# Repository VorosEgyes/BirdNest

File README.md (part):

# BirdNest ESP32-CAM Project

BirdNest is a battery-aware ESP32-CAM wildlife and bird nest monitoring project built with PlatformIO and Arduino. It captures photos on schedule or command, sends images and status updates to Telegram, and supports MQTT telemetry for smart home and IoT integrations. The firmware includes deep sleep power saving, OTA remote updates, WiFi recovery logic, DS18B20 temperature monitoring, and calibrated battery voltage reporting for reliable long-term outdoor operation.

**Single firmware binary model.** All cameras share one firmware build. Device-specific identity (label, OTA hostname, AP name) is stored in NVS at runtime, with a MAC-address-based fallback for first boot. Identity can be changed remotely via Telegram commands without reflashing.

**GitHub OTA.** Starting from v0.1.0, firmware releases are published to GitHub automatically via CI. Each device can check for and install updates over HTTPS, with SHA-256 verification and rollback support. Updates are controlled via Telegram commands at runtime. In the current firmware, the OTA install path is gated by network health and battery checks; weak RSSI alone no longer blocks installation, but the device still requires a live Wi-Fi connection and a valid OTA partition layout.

## Hardware Design Files (KiCad)

The hardware design assets are stored in `hardware/BirdNest_pcb/`.

- Schematic: `hardware/BirdNest_pcb/BirdNest_pcb.kicad_sch`
- PCB layout: `hardware/BirdNest_pcb/BirdNest_pcb.kicad_pcb`
- KiCad project: `hardware/BirdNest_pcb/BirdNest_pcb.kicad_pro`
- KiCad project local settings: `hardware/BirdNest_pcb/BirdNest_pcb.kicad_prl`
- Backup folder: `hardware/BirdNest_pcb/BirdNest_pcb-backups/`

### 3D PCB View

---

## Complete Hardware Pin Mapping (AI-Thinker ESP32-CAM)

| Function | Pin | Notes |
|---|---|---|
| XCLK | GPIO0 | 20 MHz camera clock |
| Camera D0 (Y2) | GPIO5 | Data pin |
| Camera D1 (Y3) | GPIO18 | Data pin |
| Camera D2 (Y4) | GPIO19 | Data pin |
| Camera D3 (Y5) | GPIO21 | Data pin |
| Camera D4 (Y6) | GPIO36 | Data pin |
| Camera D5 (Y7) | GPIO39 | Data pin |
| Camera D6 (Y8) | GPIO34 | Data pin |
| Camera D7 (Y9) | GPIO35 | Data pin |
| HREF | GPIO23 | Control line |
| VSYNC | GPIO25 | Control line |
| PCLK | GPIO22 | Control line |
| SDA (I2C) | GPIO26 | Camera I2C data |
| SCL (I2C) | GPIO27 | Camera I2C clock |
| OneWire (DS18B20) | GPIO13 | OneWire bus |
| ADC (Battery) | GPIO12 | Battery voltage measurement |
| Flash LED | GPIO4 | PWM control |

## Hardware modification

The current board revision uses a more elaborate power-management section around the ESP32-CAM module than the original single-regulator layout. In the current KiCad schematic, the power path is implemented with a ME2188-based regulator stage together with battery switching, UVLO sensing, and a 2.5 V reference network for battery monitoring.

Current hardware notes from the schematic:
- The firmware still targets the standard AI-Thinker ESP32-CAM pinout described above.
- The board includes battery-related nets such as BAT_RAW and BAT_MON, plus UVLO control/sense circuitry for low-voltage protection.
- The schematic also routes the DS18B20 one-wire sensor and a PIR signal net in addition to the camera and power rails.

---

## Complete Boot Sequence (PHASE 1 in setup())

1. **Serial init** — initialize UART at 115200 baud for debug output
2. **tempInit()** — DS18B20 on GPIO13 OneWire bus with internal pull-up
3. **batteryInit()** — GPIO12 ADC setup for battery voltage reading
4. **WiFi connect phase** — STA connect with boot retries; rescue captive portal on repeated failures; deep-sleep fallback when boot connectivity cannot be recovered
5. **otaInit()** and startup OTA window — check for ArduinoOTA updates (`OTA_STARTUP_WINDOW_SEC`, or `OTA_RECOVERY_WINDOW_SEC` when recovery is armed)
5b. **ghOtaInit()** — initialize GitHub OTA module after the ArduinoOTA window settles; confirm post-install rollback health if `ESP_OTA_IMG_PENDING_VERIFY`; run auto-check and install if `otaAuto=true`
6. **syncTimeIfNeeded()** — NTP sync with up to 30 retries, 200ms between each
7. **telegramInit()** and startup message processing — initialize Telegram bot and handle first message
8. **nightSleepIfNeeded()** — if after sunset, sleep until sunrise using week-number lookup table
9. **Welcome / startup photo decision** — send welcome message only on normal boot; on timer wake, capture+send photo if maintenance mode is off
10. **Final deep sleep decision** — call `esp_deep_sleep_start()` when sleep interval is enabled and OTA is not active

---

## Photo Capture Sequence (PHASE 2)

1. **cameraInit()** — configure AI-Thinker pins (D0-D7, HREF, VSYNC, PCLK, XCLK, SCCB), JPEG mode, and grab mode
2. **PSRAM profile select** — if PSRAM is present use PSRAM frame/quality flags and `fb_count=2`, otherwise fallback profile with `fb_count=1`
3. **Init resilience** — handle `ESP_ERR_INVALID_STATE` with deinit+retry, plus second init retry after 500 ms
4. **Sensor tuning** — apply white balance, AGC/AEC settings, orientation (`/mirror` and `/flip`), and light-based OV2640 register ladder
5. **Warm-up capture phase** — capture `CAMERA_WARMUP_FRAMES` frames (current active profile: 4), with frame-grab retries (`CAMERA_FB_GET_RETRIES`)
6. **Final fallback capture** — if all warm-up grabs fail, run one final retried frame-grab attempt
7. **HTTPS multipart upload** — send Telegram `sendPhoto` request with chunked JPEG write (`8 KB` chunks) over `WiFiClientSecure`
8. **Response validation** — parse response body and treat only `"ok":true` as success; store detailed failure reason otherwise
9. **Upload retry loop** — outer retry in `captureAndSendPhoto()` with WiFi reconnect and progressive backoff (`PHOTO_SEND_RETRY_BACKOFF_MS * attempt`)
10. **cameraDeinit()** — deinitialize camera and wait 100 ms before any next init

---

## Telegram Command Processing (PHASE 3 in loop())

- 5-second polling interval
- Update ID persistence every 30 seconds
- Command table: `/status`, `/help`, `/photo`, `/sleepXX`, `/maint_on`, `/maint_off`, `/netdiag`, `/reboot`, `/reboot_ota`, `/setlabel`, `/sethostname`, `/bootstrap_prepare`, `/reset_config`, `/debug0|1|2`, `/mirror0|1`, `/flip0|1`, `/battcal`, `/battcalset`, `/battcalclear`, `/mqtt`, `/mqttset`, `/mqtttopic`, `/mqtttopic_reset`, `/mqttoff`, `/otastatus`, `/otaupdate_check`, `/otaupdate_now`, `/otaupdate_auto_on`, `/otaupdate_auto_off`, `/otachannel`, `/otatoken_set`, `/otatoken_clear`
- `/status` returns status only; full command listing is in `/help`
- Callback execution for each command

---

## Deep Sleep & Wakeup (PHASE 4)

- ESP32 hibernates: CPU off, RTC timer running
- Current draw: 100–500 µA during deep sleep
- Wakeup detection via `esp_sleep_get_wakeup_cause()`
- `fromSleep` flag behavior: sets `fromSleep` to true on wake, false on normal boot

---

## Detailed Module Descriptions

### WiFi Manager
- Telegram credential check from NVS (`botToken`, `chatId`, `debugChatId`) before connect flow
- Fail-fast STA reconnect path (`WIFI_FAIL_FAST_SEC`) when captive portal is disabled
- Rescue captive portal opens on missing Telegram fields or repeated boot failures
- Persistent WiFi failure counter (`wifiFail`) in NVS; reset to 0 on successful connect

## WiFi Connection Lifecycle (full program behavior)

### 1) Boot-time connection strategy

- The device first loads Telegram credentials and WiFi failure counter from NVS.
- If captive portal is disabled and Telegram fields are present, it tries normal STA reconnect first (`wifiInit()`).
- Boot retries are applied by the main program:
	- `WIFI_BOOT_CONNECT_RETRIES`
	- `WIFI_BOOT_RETRY_BACKOFF_SEC`
- In fail-fast mode, each WiFi attempt uses `WIFI_FAIL_FAST_SEC` timeout.

### 2) Rescue captive portal fallback

- If Telegram credentials are missing, captive portal is opened immediately.
- If `WIFI_ENABLE_CAPTIVE_PORTAL != 0`, portal path is always allowed.
- With repeated STA failures, rescue portal opens after `WIFI_RESCUE_FAIL_COUNT` failures.
- Optional periodic rescue windows use `WIFI_RESCUE_PORTAL_INTERVAL_FAILS`.
- Portal timeout uses `WIFI_RESCUE_PORTAL_TIMEOUT` (rescue) or `CONFIG_PORTAL_TIMEOUT` (normal).
- Captive portal includes custom fields for Telegram token, main chat ID, and debug chat ID.

### 3) Boot failure fallback (failsafe deep sleep)

- If WiFi cannot be established after boot retries, device enters deep sleep backoff.
- Default backoff path uses `WIFI_RETRY_BACKOFF_SEC`.
- If OTA recovery is armed, recovery sleep timing is used instead (`otaGetRecoverySleepSeconds`), including low-battery protection.

### 4) Runtime link-loss handling (while running)

- The loop continuously checks WiFi state before network-heavy tasks.
- On disconnect:
	- reconnect attempts are triggered every `WIFI_RUNTIME_RECONNECT_INTERVAL_SEC`
	- diagnostics counters are updated (`/netdiag`)
- If disconnected too long, failsafe reboot is triggered after `WIFI_RUNTIME_REBOOT_AFTER_SEC`.

### 5) OTA interaction

- OTA processing runs first in loop (`otaLoop()`).
- While OTA is active, other network work is deferred.
- Deep sleep is suppressed during active OTA transfer.
- Startup OTA polling window is dynamic: normal `OTA_STARTUP_WINDOW_SEC`, or extended `OTA_RECOVERY_WINDOW_SEC` when recovery mode is armed.
- OTA transfer watchdog restarts the device if no OTA events arrive for `OTA_STALL_TIMEOUT_SEC`.

### 6) Maintenance mode behavior

- Maintenance mode suppresses automatic sleep/photo cycle decisions, but does not bypass WiFi requirements.
- If network quality is poor, runtime reconnect/failsafe logic still applies.
- Manual diagnostics command: `/netdiag`.

### Telegram
- Bot token stored in NVS
- Poll loop every 5 seconds
- NVS persistence of sleep/maintenance settings
- `lastMsgId` tracking for message updates
- `/help` provides the full command list, while `/status` stays focused on runtime state

### Camera
- AI-Thinker pin mapping: D0–D7 data, HREF/VSYNC/PCLK control, XCLK 20 MHz
- PSRAM-aware frame profile (`CAMERA_FRAMESIZE_*`, `CAMERA_JPEG_QUALITY_*`, `fb_count`)
- Warm-up frames from build flag (`CAMERA_WARMUP_FRAMES`, active profile uses 4)
- JPEG capture and frame buffer
- Upload via HTTPS multipart POST using `WiFiClientSecure` and `writeAll()` helper
- Manual lowlight/day exposure register ladder based on ambient light register (`0x2f`)
- Multi-attempt Telegram photo upload with reconnect/backoff on failure
- Remote error diagnostics via Telegram debug messages (serial not required)

### Camera Exposure / Lowlight Logic (actual implementation)
- Ambient light value is read from sensor register `0x2f`
- `CAMERA_DAY_THRESHOLD` separates lowlight and daylight branches
- AGC is disabled (`set_gain_ctrl(0)`), gain is manual (`set_agc_gain(0)`), and exposure is controlled by register ladder writes
- A post-frame fine-tuning pass adjusts `0x47`, `0x2a`, and `0x2b` for very low to medium light
- Current implementation does not use `CAMERA_DYNAMIC_EXPOSURE_PROFILE`, `CAMERA_DAY_*`, or `CAMERA_LOWLIGHT_*` flag families

### Photo Upload Reliability and Remote Diagnostics
- Upload attempts are retried with progressive backoff and WiFi reconnect between tries.
- Retry behavior is configurable with:
	- `PHOTO_SEND_MAX_RETRIES`
	- `PHOTO_SEND_RETRY_BACKOFF_MS`
	- `CAMERA_FB_GET_RETRIES`
	- `CAMERA_FB_GET_RETRY_DELAY_MS`
- On each failed attempt, the device sends detailed failure reason to Telegram debug chat.
- Final failure message includes the last known upload error cause.

Common remote error reasons (`cameraGetLastError`):

- `empty_chat_id` - no chat ID was provided
- `missing_bot_token` - Telegram bot token is missing/empty
- `wifi_not_connected_before_upload` - WiFi dropped before upload start
- `telegram_tls_connect_failed` - TLS connection to `api.telegram.org:443` failed
- `camera_fb_get_failed_final` - frame grab failed after warm-up and final fallback attempt
- `upload_failed_headers_or_prefix` - multipart request header/prefix write failed
- `upload_chunk_write_failed_offset_N` - JPEG data upload interrupted at byte offset
- `upload_multipart_tail_failed` - multipart tail write failed
- `telegram_response_not_ok_empty_body` - Telegram returned non-OK with empty body
- `telegram_response_not_ok_...` - Telegram API responded with `ok:false` and body snippet

### Temperature
- DS18B20 on GPIO13 OneWire protocol with internal pull-up
- One blocking conversion is performed on cache miss; the result is reused for up to 60 seconds across status, MQTT, and photo-caption reads.
- If no sensor is detected during initialization, reads return `-127.0` without polling the OneWire bus.

### Battery
- ADC on GPIO12 with resistor divider formula
- Two-point calibration math using `bCalA`/`bCalB`
- GPIO12 is ADC2 on ESP32. While WiFi is connected, ADC2 sampling is not reliable/available, so the firmware returns the last cached valid value.
- A fresh battery sample is taken during boot before WiFi connect (`batteryRefresh()` in setup), then reused during active WiFi on ADC2 hardware.
- `/status` reports that cached value on ADC2+WiFi. This is typically the most recent wake-time sample.
- If `/status` is sent while the device is in deep sleep, it is processed after wake, so battery data in the reply reflects the new measurement from that wake cycle.

### Runtime Device Identity

All cameras run the same firmware binary. Each device's identity is stored in NVS and loaded at every boot.

| NVS key | Default | Description |
|---|---|---|
| `devLabel` | `BirdNest-XXXXXXXX` (MAC) | Human-readable device name |
| `otaHost` | `birdnest-xxxxxxxx` (MAC) | ArduinoOTA mDNS hostname |
| AP name | derived from `devLabel` + `-cfg` | Captive portal AP name (not stored separately) |

On first boot the label and hostname are generated from the lower 32 bits of the chip MAC address, so multiple devices with the same factory firmware never collide on the same LAN.

Telegram commands:
- `/setlabel <name>` — change device label (persisted in NVS, affects MQTT topics and photo captions)
- `/sethostname <name>` — change ArduinoOTA hostname (reboot required to apply mDNS)
- `/status` and welcome message show current label and OTA hostname

---

### ArduinoOTA (local network upload)
- Startup OTA window: `OTA_STARTUP_WINDOW_SEC` (default 8 s)
- Extended recovery window: `OTA_RECOVERY_WINDOW_SEC` (default 120 s) when recovery latch is armed
- OTA stall watchdog: restart if transfer is idle for `OTA_STALL_TIMEOUT_SEC`
- Recovery sleep policy: `OTA_RECOVERY_SLEEP_SEC`, with low-battery fallback `OTA_RECOVERY_LOW_BATTERY_SLEEP_SEC` below `OTA_RECOVERY_MIN_BATTERY_V`
- Recovery state is persisted in NVS via `otaArmed` and `otaCycles`
- `/reboot_ota` arms recovery and reboots — opens an extended OTA window for PlatformIO upload

---

### GitHub OTA (automatic over-the-internet updates)

Starting from v0.1.0, every `v*` git tag triggers a CI build that publishes a single firmware binary and `ota-manifest.json` to GitHub Releases. Devices can check and install these releases over HTTPS without physical access.

#### How it works

1. **Check**: device queries `api.github.com/repos/VorosEgyes/BirdNest/releases`, finds the best candidate by SemVer and channel (stable/beta), downloads `ota-manifest.json`.
2. **Install gate**: battery ≥ max(3.60 V, `manifest.min_battery_v`), WiFi stable.
3. **Install**: streams the `.bin` via HTTPS, verifies SHA-256 incrementally, writes to the inactive OTA partition, reboots.
4. **Health confirm**: on first boot after install, pings `api.github.com/rate_limit` up to 3 times; if any succeed, marks the image valid and cancels rollback.

#### Partition table requirement

GitHub OTA install requires an A/B OTA partition layout (`partitions_ota_4m.csv`). Devices previously flashed with `min_spiffs.csv` (single app partition) will run all GitHub OTA code normally but **install will be blocked** with reason `no_update_partition` until the device receives a full flash. This is why the first installation should be done over USB/serial for a new or previously single-partition device.

| Scenario | ArduinoOTA upload | GitHub OTA install |
|---|---|---|
| Device with `partitions_ota_4m.csv` | ✅ | ✅ |
| Device with `min_spiffs.csv` (old layout) | ✅ | ❌ blocked |

#### First-install / partition migration guide

To migrate an existing camera from `min_spiffs` to OTA partitions:

1. Connect via USB.
2. Run a full flash (includes partition table + bootloader + firmware):
   ```bash
   pio run -e cam1 -t upload --upload-port /dev/cu.usbserial-XXXX
   # or cam2, cam3, cam4 — all envs produce the same binary
   ```
3. After this one-time flash, all future updates can be done via GitHub OTA with no physical access.

For cameras only reachable via ArduinoOTA, use `/bootstrap_prepare` before the USB flash session to ensure maintenance mode is on and sleep is off.

#### Bootstrap preflight command

`/bootstrap_prepare` — run this before any first-install or partition migration session:
- Sets maintenance mode ON (suppresses deep sleep)
- Sets sleep interval to 0
- Disables WiFi modem sleep
- Arms ArduinoOTA recovery
- Runs and reports a preflight check:
  - Battery ≥ `BOOTSTRAP_MIN_BATTERY_V` (default 3.80 V)
  - WiFi connected and RSSI ≥ `BOOTSTRAP_MIN_RSSI_DBM` (default −82 dBm)
  - Telegram credentials present
  - OTA update partition reachable

Reports `READY` or `NOT READY` with per-check detail.

#### GitHub OTA Telegram commands

| Command | Description |
|---|---|
| `/otastatus` | JSON status: current version, channel, auto mode, pending target, last reason |
| `/otaupdate_check` | Query GitHub releases; report available version or no-update |
| `/otaupdate_now` | Check and immediately install if update found |
| `/otaupdate_auto_on` | Enable automatic check+install on every boot |
| `/otaupdate_auto_off` | Disable automatic updates (manual only) |
| `/otachannel stable\|beta` | Switch release channel |
| `/otatoken_set <token>` | Set GitHub API token (private repos; message auto-deleted) |
| `/otatoken_clear` | Clear token; drops pending private target |

#### Versioning and CI release workflow

- `FW_VERSION` is injected at build time from the nearest git tag via `scripts/fw_version_from_git.py`.
- Local/untagged builds use `0.0.0-dev` as fallback.
- The shared PlatformIO environment pins `espressif32@7.0.1` (Arduino ESP32
  2.x); upgrading to Arduino ESP32 3.x requires camera and OTA API migration.
- CI (`release-ota.yml`) triggers on any `v*` tag push:
  - Builds `[env:release]` (same binary as camX envs)
  - Calculates SHA-256
  - Uploads `birdnest-esp32cam-vX.Y.Z.bin` and `ota-manifest.json` to GitHub Releases
- Devices on stable channel only see non-prerelease tags; beta channel sees prerelease tags too.

#### Check/backoff policy

- Auto-check runs at most once per day (`GH_OTA_DAILY_CHECK_SEC`).
- WiFi instability increments a fail streak with exponential backoff: 6 h → 12 h → 24 h → 48 h max.
- Backoff is reset after 2 consecutive stable WiFi cycles.
- Manual `/otaupdate_check` and `/otaupdate_now` bypass daily interval and backoff.
- The Telegram TLS connection is closed before the automatic GitHub health probe.
  The probe parses only the rate-limit field it needs; failures report HTTP,
  transport, response length and JSON parsing details through Telegram.
  If an automatic check ends in a crash, the next boot disables automatic checks
  and reports the retained OTA stage and minimum free task stack in bytes through
  Telegram. Manual checks remain available; use `/otaupdate_auto_on` to retry.

#### GitHub OTA NVS keys (namespace: `birdnest_gh`)

| Key | Type | Description |
|---|---|---|
| `otaAuto` | bool | Auto-update enabled |
| `otaChannel` | string | `stable` or `beta` |
| `otaToken` | string | GitHub API token (private repos) |
| `otaLastChk` | uint32 | Unix timestamp of last successful check |
| `otaWifiFail` | uint16 | Consecutive WiFi stability failures |
| `otaChkFail` | uint16 | Consecutive check failures |
| `otaWifiOk` | uint8 | Consecutive stable cycles (for backoff reset) |
| `otaBackoff` | uint32 | Backoff-end timestamp (0 = no backoff) |
| `otaTarget` | string | JSON-serialized pending install target |
| `otaLastReason` | string | Last OTA block/fail reason code |
| `otaRebootFlg` | bool | Set before install reboot, cleared on next boot |
| `otaLastTgt` | string | Version string of last attempted install |

### MQTT
- Runtime MQTT client with automatic reconnect
- JSON status publish to a configurable state topic (channel)
- Config stored in NVS and editable from Telegram
- Supports auth and no-auth brokers
- Periodic publish (`MQTT_STATUS_INTERVAL_SEC`) and immediate publish on boot/config change
- LWT availability support (`online` / `offline`, retained)
- Separate state/event/availability topic model
- Payload schema versioning (`schema_version`)
- GitHub OTA events published via `mqttPublishOtaEvent()` to the event topic

---

## MQTT Setup and Usage

### Default Topics

If no custom topic is set, these topics are used:

- State topic: `birdnest/<deviceLabel>/status`
- Event topic: `birdnest/<deviceLabel>/event`
- Availability topic: `birdnest/<deviceLabel>/availability`

Where `<deviceLabel>` is the runtime device identity loaded from NVS (see Runtime Device Identity section). The default is `BirdNest-XXXXXXXX` based on MAC address.

If you set a custom topic with `/mqtttopic`:

- The custom value is used as the state topic.
- If it ends with `/status`, event and availability are derived as sibling topics.
- Otherwise `/event` and `/availability` are appended.

### Telegram Commands for MQTT

- `/mqtt` - show current MQTT config and active channel
- `/mqttset <ip-or-host> <port> <user|-> <pass|->` - set broker and auth in one message
- `/mqtttopic <topic>` - set custom publish channel/topic
- `/mqtttopic_reset` - reset topic to default (`birdnest/CAMERA_LABEL/status`)
- `/mqttoff` - disable MQTT and clear broker credentials

`/mqtt` now reports:

- State topic
- Event topic
- Availability topic
- Schema version

### One-message setup examples

- Auth enabled:
	- `/mqttset 192.168.1.100 1883 mqtt_user mqtt_pass`
- No auth:
	- `/mqttset 192.168.1.100 1883 - -`

### Channel/topic examples

- Set custom channel:
	- `/mqtttopic birdnest/BirdNestCam1/status`
- Reset to default channel:
	- `/mqtttopic_reset`

### Published payloads

State payload (`status`) is JSON and includes:

- `schema_version`
- `device`
- `reason` (`boot`, `periodic`, `manual`, `config_updated`, ...)
- `ip`
- `rssi`
- `uptime_s`
- `temp_c`
- `battery_v`
- `battery_pct`
- `maint`

Event payload (`event`) is JSON and includes:

- `schema_version`
- `device`
- `event`
- `detail`
- `uptime_s`

GitHub OTA event payload additionally includes:

- `reason` — machine-readable reason code (e.g. `no_update`, `battery_low`, `sha256_mismatch`)
- `current_version` — running firmware version
- `target_version` — target version being installed (empty if check-only)
- `channel` — `stable` or `beta`

OTA event types: `ota_check_start`, `ota_check_no_update`, `ota_update_available`, `ota_install_blocked`, `ota_update_start`, `ota_update_progress`, `ota_update_ok`, `ota_update_fail`, `ota_check_fail`

Availability payload (`availability`) values:

- `online` (retained on successful connect)
- `offline` (retained via LWT or explicit MQTT disable)

---

## NVS Storage Structure

All keys live in the `birdnest` namespace unless otherwise noted.

### Device identity

| Key | Type | Description |
|---|---|---|
| `devLabel` | string | Runtime device label (default: `BirdNest-XXXXXXXX`) |
| `otaHost` | string | ArduinoOTA mDNS hostname (default: `birdnest-xxxxxxxx`) |

### Telegram credentials and runtime config

| Key | Type | Description |
|---|---|---|
| `botToken` | string | Telegram bot token |
| `chatId` | string | Telegram main chat ID |
| `debugChatId` | string | Telegram debug chat ID |
| `sleepSec` | uint32 | Deep sleep interval in seconds |
| `maintMode` | bool | Maintenance mode |
| `dbgVerb` | uint8 | Debug verbosity (0–2) |
| `camMirror` | bool | Camera mirror |
| `camFlip` | bool | Camera vertical flip |
| `lastMsgId` | int32 | Last processed Telegram update ID |

### Battery calibration

| Key | Type | Description |
|---|---|---|
| `bCalEn` | bool | Two-point calibration enabled |
| `bCalA` / `bCalB` | float | Calibration slope / offset |
| `bCalRV1/MV1/RV2/MV2` | float | Calibration reference points |

### ArduinoOTA recovery

| Key | Type | Description |
|---|---|---|
| `otaArmed` | bool | Recovery mode armed |
| `otaCycles` | uint16 | Recovery cycles remaining |

### WiFi

| Key | Type | Description |
|---|---|---|
| `wifiFail` | uint16 | Consecutive WiFi boot failure counter |

### MQTT

| Key | Type | Description |
|---|---|---|
| `mqttHost` | string | Broker host/IP |
| `mqttPort` | uint16 | Broker port |
| `mqttUser` | string | Username (optional) |
| `mqttPass` | string | Password (optional) |
| `mqttTopic` | string | Custom state topic (optional) |

### GitHub OTA (namespace: `birdnest_gh`)

| Key | Type | Description |
|---|---|---|
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
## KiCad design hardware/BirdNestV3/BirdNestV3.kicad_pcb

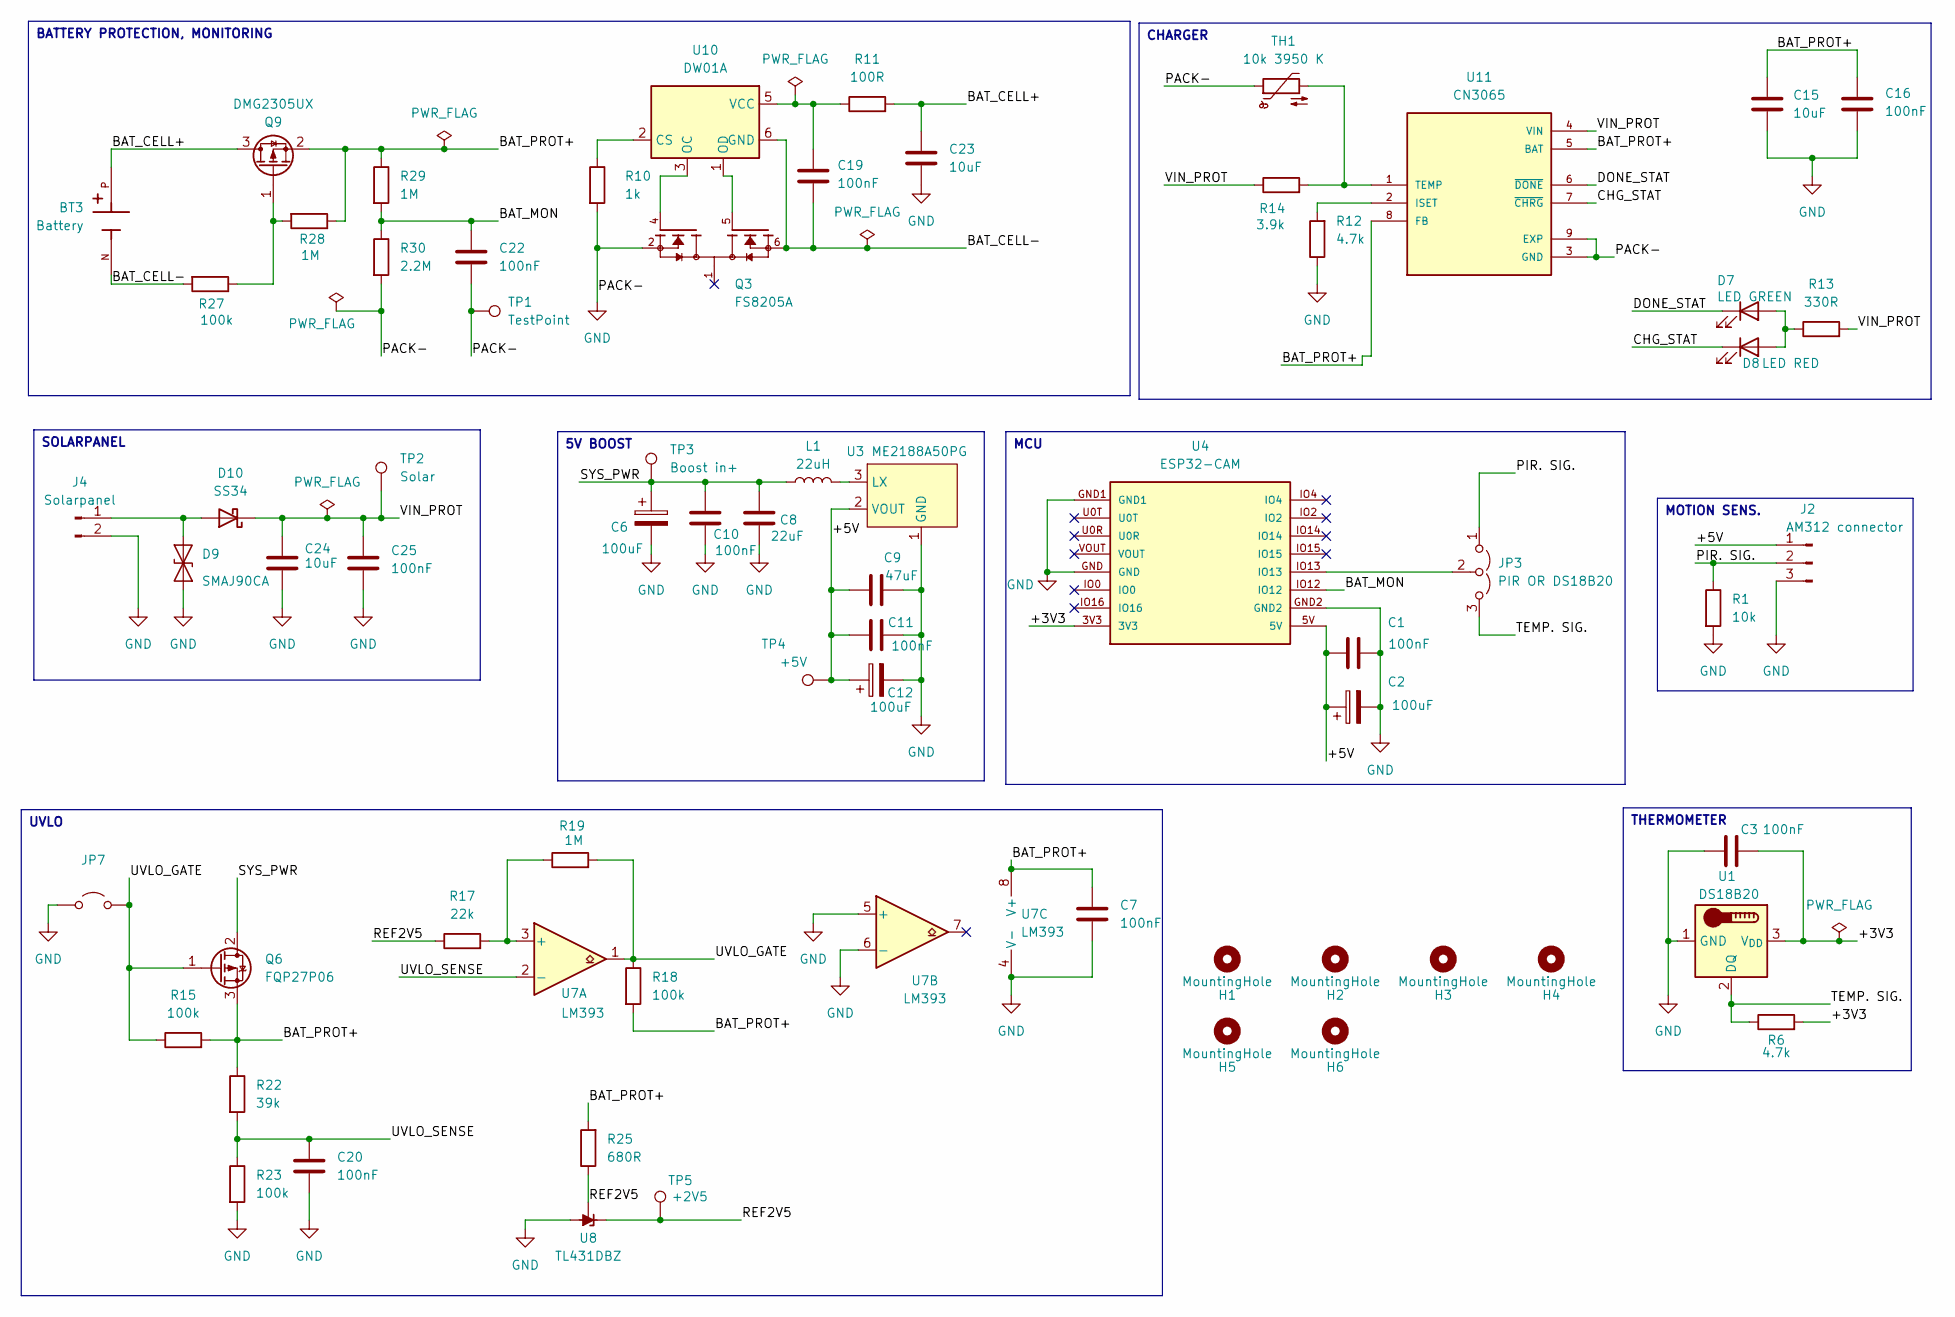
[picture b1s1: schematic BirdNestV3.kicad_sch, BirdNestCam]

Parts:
BT3: Battery; BAT_1042; PARTREV E
C1, C3, C7, C10, C11, C16, C19, C20, C22, C25: 100nF; C_1206_3216Metric_Pad1.33x1.80mm_HandSolder
C2, C6, C12: 100uF; CP_Radial_D6.3mm_P2.50mm
C8: 22uF; C_1206_3216Metric_Pad1.33x1.80mm_HandSolder
C9: 47uF; C_1206_3216Metric_Pad1.33x1.80mm_HandSolder
C15, C23, C24: 10uF; C_1206_3216Metric_Pad1.33x1.80mm_HandSolder
D7: LED GREEN; LED_0805_2012Metric
D8: LED RED; LED_0805_2012Metric
D9: SMAJ90CA; D_SMA
D10: SS34; D_SMA
H1, H2, H3, H4: MountingHole; MountingHole_3.2mm_M3
H5, H6: MountingHole; CableTieHole_5.3mm
J2: AM312 connector; TerminalBlock_Phoenix_MKDS-1,5-3-5.08_1x03_P5.08mm_Horizont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
J4: Solarpanel; TerminalBlock_Phoenix_MKDS-1,5-2-5.08_1x02_P5.08mm_Horizont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
JP3: PIR OR DS18B20; PinHeader_1x03_P2.54mm_Vertical
JP7: Jumper_2_Open; PinHeader_1x02_P2.54mm_Vertical
L1: 22uH; L_10.4x10.4_H4.8
Q3: FS8205A; SOP65P640X120-8N; PARTREV 1.7
Q6: FQP27P06; TO-220-3_Vertical
Q9: DMG2305UX; SOT23
R1: 10k; R_1206_3216Metric_Pad1.30x1.75mm_HandSolder
R6, R12: 4.7k; R_1206_3216Metric_Pad1.30x1.75mm_HandSolder
R10: 1k; R_1206_3216Metric_Pad1.30x1.75mm_HandSolder
R11: 100R; R_1206_3216Metric_Pad1.30x1.75mm_HandSolder
R13: 330R; R_1206_3216Metric_Pad1.30x1.75mm_HandSolder
R14: 3.9k; R_1206_3216Metric_Pad1.30x1.75mm_HandSolder
R15, R18, R23, R27: 100k; R_1206_3216Metric_Pad1.30x1.75mm_HandSolder
R17: 22k; R_1206_3216Metric_Pad1.30x1.75mm_HandSolder
R19, R28, R29: 1M; R_1206_3216Metric_Pad1.30x1.75mm_HandSolder
R22: 39k; R_1206_3216Metric_Pad1.30x1.75mm_HandSolder
R25: 680R; R_1206_3216Metric_Pad1.30x1.75mm_HandSolder
R30: 2.2M; R_1206_3216Metric_Pad1.30x1.75mm_HandSolder
TH1: 10k 3950 K; PinHeader_1x02_P1.00mm_Vertical
TP1: TestPoint; TestPoint_Pad_D3.0mm
TP2: Solar; TestPoint_Pad_D3.0mm
TP3: Boost in+; TestPoint_Pad_D3.0mm
TP4: +5V; TestPoint_Pad_D3.0mm
TP5: +2V5; TestPoint_Pad_D3.0mm
U1: DS18B20; TO-92_Inline
U3: ME2188A50PG; SOT-89-3
U4: ESP32-CAM
U7: LM393; DIP-8_W7.62mm
U8: TL431DBZ; SOT-23
U10: DW01A; SOT-23-6
U11: CN3065; DFN300X300X90-9N

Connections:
/+3V3: C3.2, R6.2, U1.3 (V_{DD}), U4.3V3
/+5V: C1.1, C2.1, C9.1, C11.2, C12.1, J2.1, TP4.1 (1_1), U3.2 (VOUT), U4.5V
/BAT_CELL+: BT3.P, C23.1, Q9.3 (D), R11.2
/BAT_CELL-: BT3.N, C19.2, Q3.6, Q3.7, R27.2, U10.6 (GND)
/BAT_MON: C22.1, R29.2, R30.1, U4.IO12
/BAT_PROT+: C7.1, C15.1, C16.1, Q6.3 (S), Q9.2 (S), R15.2, R18.2, R22.1, R25.2, R28.1, R29.1, U7.8 (V+), U11.5 (BAT), U11.8 (FB)
/CHG_STAT: D8.1 (K), U11.7 (~CHRG)
/DONE_STAT: D7.1 (K), U11.6 (~DONE)
/PIR. SIG.: J2.2, JP3.1 (A), R1.1
/REF2V5: R17.1, R25.1, TP5.1 (1_1), U8.1 (K), U8.2 (REF)
/SYS_PWR: C6.1, C8.1, C10.1, L1.1, Q6.2 (D), TP3.1 (1_1)
/TEMP. SIG.: JP3.3 (B), R6.1, U1.2 (DQ)
/UVLO_GATE: JP7.2 (B), Q6.1 (G), R15.1, R18.1, R19.2, U7.1
/UVLO_SENSE: C20.1, R22.2, R23.1, U7.2 (-)
/VIN_PROT: C24.1, C25.1, D10.1 (K), R13.2, R14.1, TP2.1 (1_1), U11.4 (VIN)
GND: C1.2, C2.2, C3.1, C6.2, C7.2, C8.2, C9.2, C10.2, C11.1, C12.2, C15.2, C16.2, C20.2, C22.2, C23.2, C24.2, C25.2, D9.1 (A1), J2.3, J4.2, JP7.1 (A), Q3.2, Q3.3, R1.2, R10.2, R12.1, R23.2, R30.2, TH1.1, TP1.1 (1_1), U1.1 (GND), U3.1 (GND), U4.GND, U4.GND1, U4.GND2, U7.4 (V-), U7.5 (+), U7.6 (-), U8.3 (A), U11.3 (GND), U11.9 (EXP)
unnamed: D7.2 (A), D8.2 (A), R13.1
unnamed: D9.2 (A2), D10.2 (A), J4.1
unnamed: JP3.2 (C), U4.IO13
unnamed: Q9.1 (G), R27.1, R28.2
unnamed: L1.2, U3.3 (LX)
unnamed: R17.2, R19.1, U7.3 (+)
unnamed: R10.1, U10.2 (CS)
unnamed: Q3.4, U10.3 (OC)
unnamed: Q3.5, U10.1 (OD)
unnamed: C19.1, R11.1, U10.5 (VCC)
unnamed: R12.2, U11.2 (ISET)
unnamed: R14.2, TH1.2, U11.1 (TEMP)

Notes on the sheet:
CHARGER
MCU
5V BOOST
BATTERY PROTECTION, MONITORING
SOLARPANEL
MOTION SENS.
UVLO
THERMOMETER

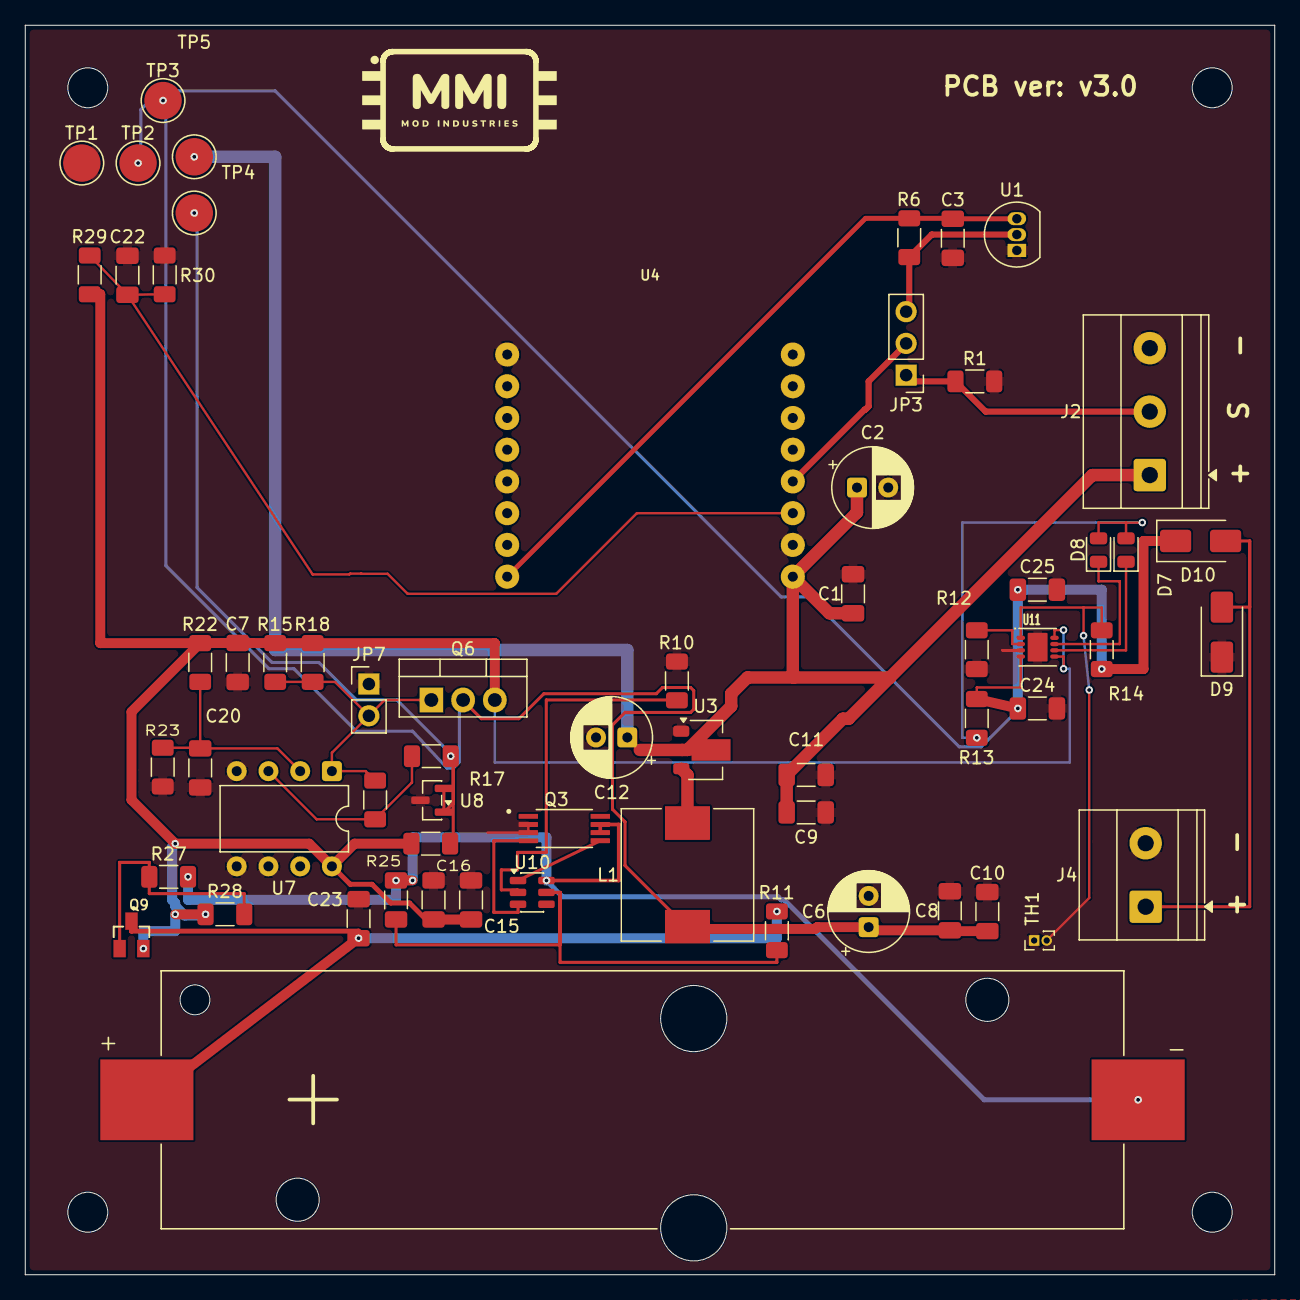
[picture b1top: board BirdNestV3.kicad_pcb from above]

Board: 2 copper layers, 100.0 x 100.0 mm, 68 parts (0 on the bottom side), 28 nets.

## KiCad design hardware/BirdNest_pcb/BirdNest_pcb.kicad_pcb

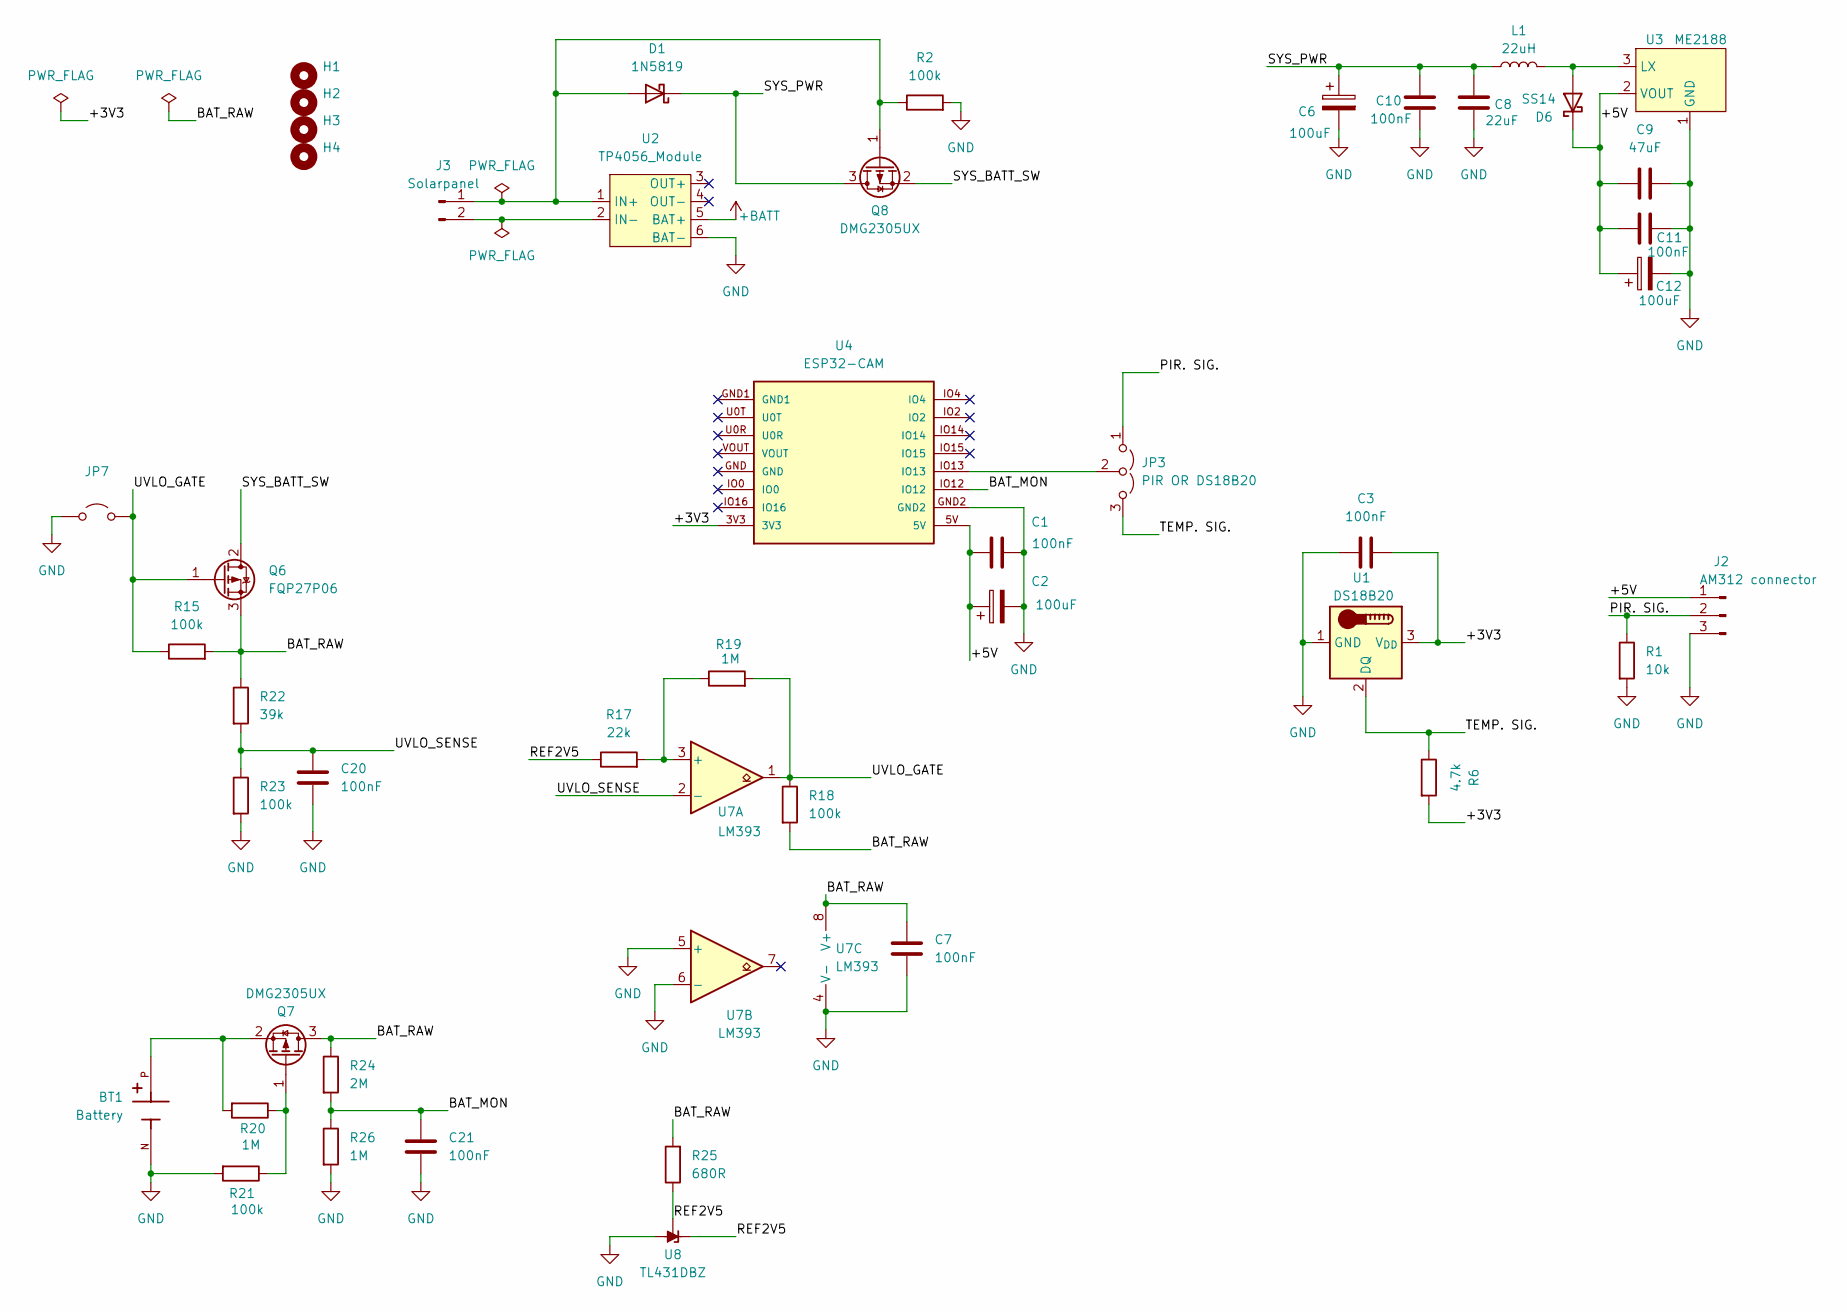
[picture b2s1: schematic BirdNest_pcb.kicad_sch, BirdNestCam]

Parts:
BT1: Battery; BAT_1042; PARTREV E
C1, C3, C7, C10, C11, C20, C21: 100nF; C_1206_3216Metric_Pad1.33x1.80mm_HandSolder
C2, C6, C12: 100uF; CP_Radial_D6.3mm_P2.50mm
C8: 22uF; C_1206_3216Metric_Pad1.33x1.80mm_HandSolder
C9: 47uF; C_1206_3216Metric_Pad1.33x1.80mm_HandSolder
D1: 1N5819; D_DO-41_SOD81_P10.16mm_Horizontal
D6: SS14; D_SMA-SMB_Universal_Handsoldering
H1, H2, H3, H4: MountingHole; MountingHole_3.2mm_M3
J2: AM312 connector; TerminalBlock_Phoenix_MKDS-1,5-3-5.08_1x03_P5.08mm_Horizont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
J3: Solarpanel; TerminalBlock_Phoenix_MKDS-1,5-2-5.08_1x02_P5.08mm_Horizont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
JP3: PIR OR DS18B20; PinHeader_1x03_P2.54mm_Vertical
JP7: Jumper_2_Open; PinHeader_1x02_P2.54mm_Vertical
L1: 22uH; L_10.4x10.4_H4.8
Q6: FQP27P06; TO-220-3_Vertical
Q7, Q8: DMG2305UX; SOT23
R1: 10k; R_1206_3216Metric_Pad1.30x1.75mm_HandSolder
R2, R15, R18, R21, R23: 100k; R_1206_3216Metric_Pad1.30x1.75mm_HandSolder
R6: 4.7k; R_1206_3216Metric_Pad1.30x1.75mm_HandSolder
R17: 22k; R_1206_3216Metric_Pad1.30x1.75mm_HandSolder
R19, R20, R26: 1M; R_1206_3216Metric_Pad1.30x1.75mm_HandSolder
R22: 39k; R_1206_3216Metric_Pad1.30x1.75mm_HandSolder
R24: 2M; R_1206_3216Metric_Pad1.30x1.75mm_HandSolder
R25: 680R; R_1206_3216Metric_Pad1.30x1.75mm_HandSolder
U1: DS18B20; TO-92_Inline
U2: TP4056_Module; TP4056-Module
U3: ME2188; SOT-89-3
U4: ESP32-CAM
U7: LM393; DIP-8_W7.62mm
U8: TL431DBZ; SOT-23

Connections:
+BATT: U2.5 (BAT+)
/+3V3: C3.2, R6.2, U1.3 (V_{DD}), U4.3V3
/+5V: C1.1, C2.1, C9.1, C11.2, C12.1, D6.1 (K), J2.1, U3.2 (VOUT), U4.5V
/BAT_MON: C21.1, R24.2, R26.1, U4.IO12
/BAT_RAW: C7.1, Q6.3 (S), Q7.3 (D), R15.2, R18.2, R22.1, R24.1, R25.2, U7.8 (V+)
/PIR. SIG.: J2.2, JP3.1 (A), R1.1
/REF2V5: R17.1, R25.1, U8.1 (K), U8.2 (REF)
/SYS_BATT_SW: Q6.2 (D), Q8.2 (S)
/SYS_PWR: C6.1, C8.1, C10.1, D1.1 (K), L1.1, Q8.3 (D)
/TEMP. SIG.: JP3.3 (B), R6.1, U1.2 (DQ)
/UVLO_GATE: JP7.2 (B), Q6.1 (G), R15.1, R18.1, R19.2, U7.1
/UVLO_SENSE: C20.1, R22.2, R23.1, U7.2 (-)
GND: BT1.N, C1.2, C2.2, C3.1, C6.2, C7.2, C8.2, C9.2, C10.2, C11.1, C12.2, C20.2, C21.2, J2.3, JP7.1 (A), R1.2, R2.2, R21.2, R23.2, R26.2, U1.1 (GND), U2.6 (BAT-), U3.1 (GND), U4.GND2, U7.4 (V-), U7.5 (+), U7.6 (-), U8.3 (A)
unnamed: D1.2 (A), J3.1, Q8.1 (G), R2.1, U2.1 (IN+)
unnamed: D6.2 (A), L1.2, U3.3 (LX)
unnamed: J3.2, U2.2 (IN-)
unnamed: JP3.2 (C), U4.IO13
unnamed: Q7.1 (G), R20.1, R21.1
unnamed: BT1.P, Q7.2 (S), R20.2
unnamed: R17.2, R19.1, U7.3 (+)

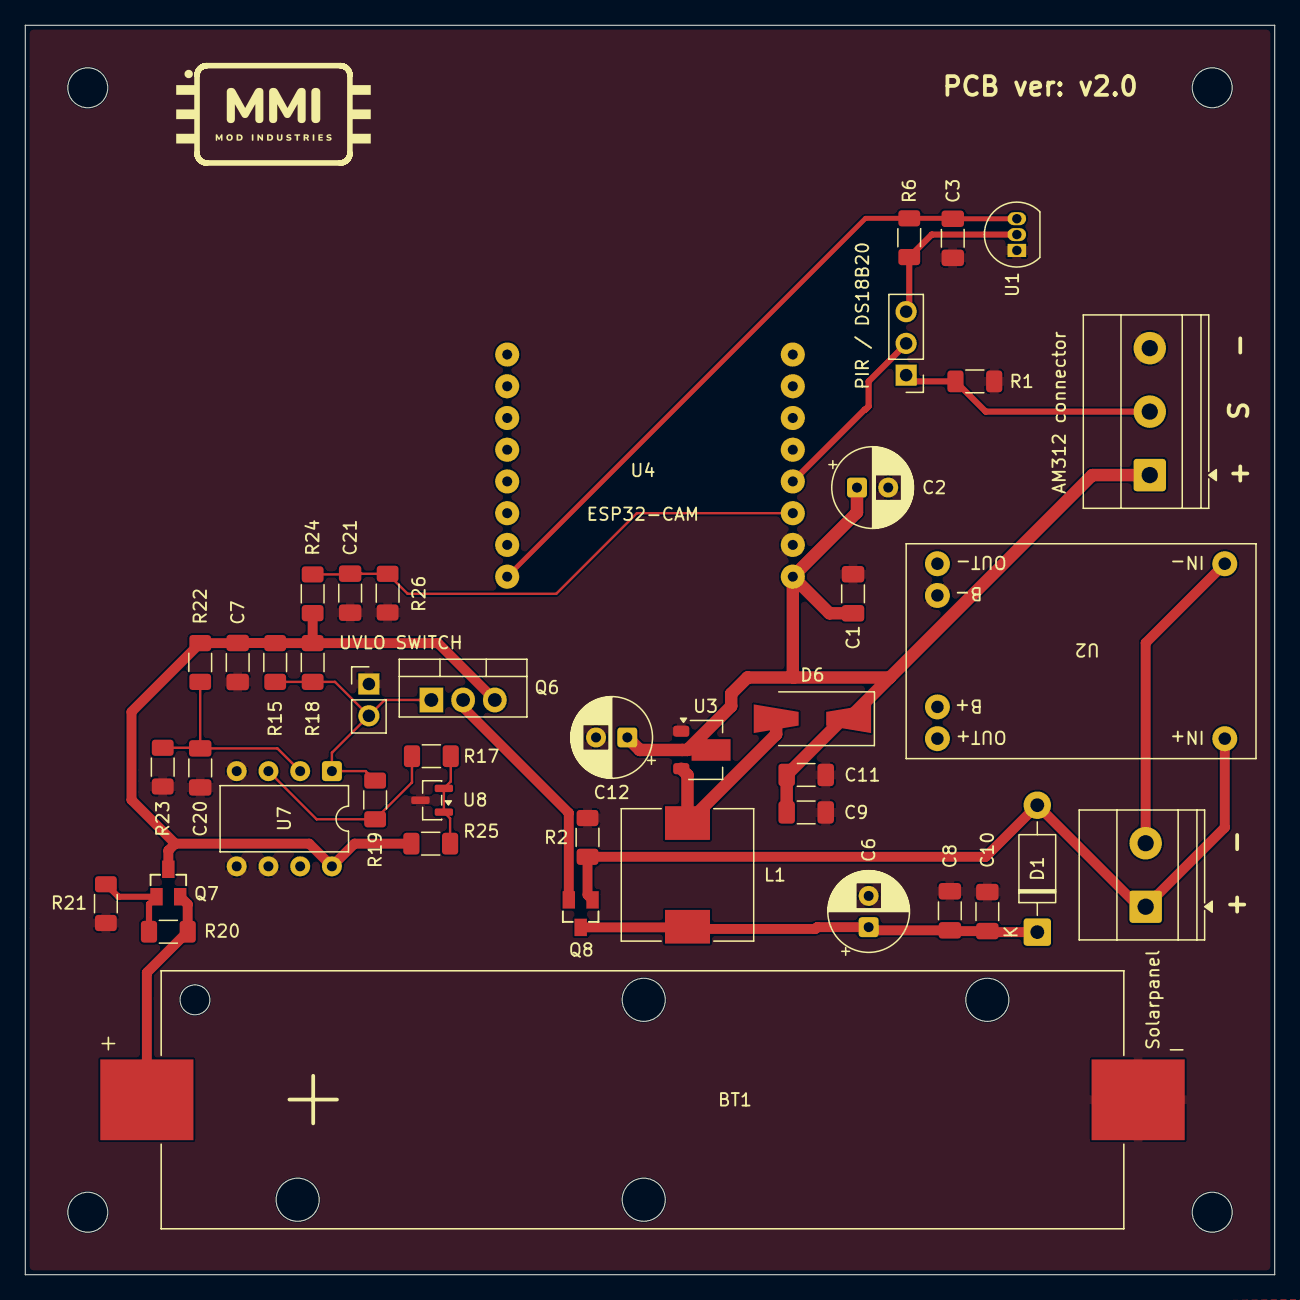
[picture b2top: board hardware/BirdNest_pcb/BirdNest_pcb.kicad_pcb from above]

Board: 2 copper layers, 100.0 x 100.0 mm, 47 parts (0 on the bottom side), 19 nets.

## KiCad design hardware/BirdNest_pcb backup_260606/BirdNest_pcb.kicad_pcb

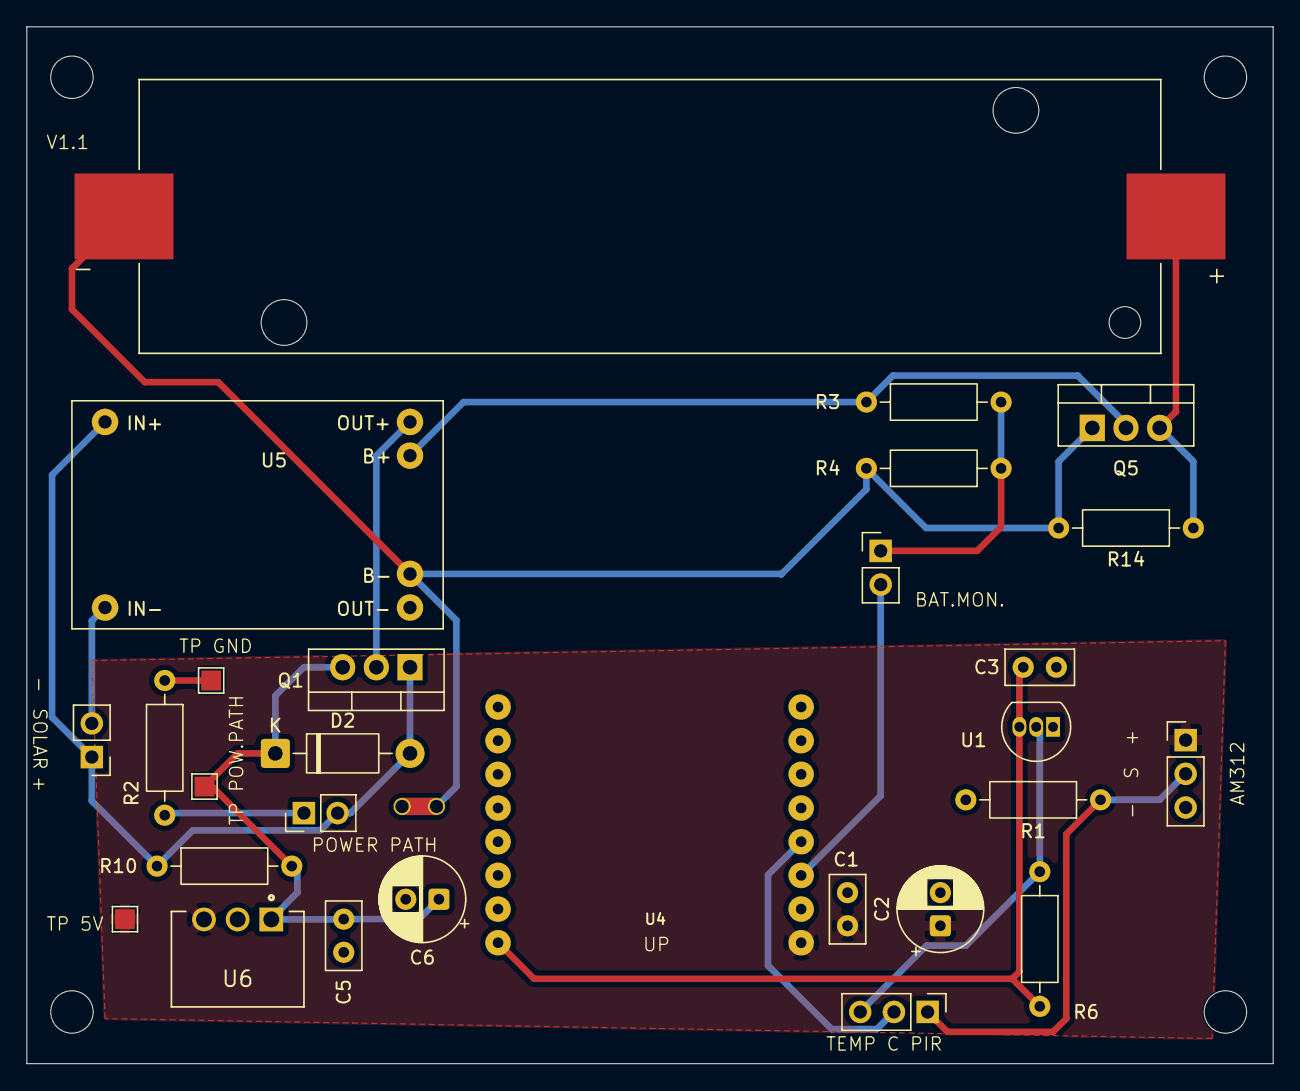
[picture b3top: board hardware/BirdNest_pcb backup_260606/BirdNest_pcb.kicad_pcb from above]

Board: 2 copper layers, 94.0 x 78.2 mm, 33 parts (0 on the bottom side), 16 nets.

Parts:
BT1: Battery; BAT_1042
C1, C3, C5: 100nF; C_Disc_D5.0mm_W2.5mm_P2.50mm
C2, C6: 100uF; CP_Radial_D6.3mm_P2.50mm
D2: 1N5819; D_DO-41_SOD81_P10.16mm_Horizontal
H1, H2, H3, H4: MountingHole; MountingHole_3.2mm_M3
J1: Solarpanel; PinHeader_1x02_P2.54mm_Vertical
J2: AM312 connector; PinHeader_1x03_P2.54mm_Vertical
JP1, JP2: Jumper_2_Open; PinHeader_1x02_P2.54mm_Vertical
JP3: PIR OR DS18B20; PinHeader_1x03_P2.54mm_Vertical
NT2: NetTie_2; NetTie-2_THT_Pad1.0mm
Q1, Q5: FQP27P06; TO-220-3_Vertical
R1, R2, R14: 10k; R_Axial_DIN0207_L6.3mm_D2.5mm_P10.16mm_Horizontal
R3: 1,5M; R_Axial_DIN0207_L6.3mm_D2.5mm_P10.16mm_Horizontal
R4: 1M; R_Axial_DIN0207_L6.3mm_D2.5mm_P10.16mm_Horizontal
R6: 4.7k; R_Axial_DIN0207_L6.3mm_D2.5mm_P10.16mm_Horizontal
R10: 100k; R_Axial_DIN0207_L6.3mm_D2.5mm_P10.16mm_Horizontal
TP1, TP2, TP3: TestPoint; TestPoint_Pad_1.5x1.5mm
U1: DS18B20; TO-92_Inline
U4: ESP32-CAM
U5: TP4056_Module; TP4056-Module
U6: VXO7803-500; CONV_VXO7803-500

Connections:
+BATT: Q5.2 (D), R3.1, U5.5 (BAT+)
-BATT: BT1.N, NT2.1, Q5.1 (G), R4.2, R14.2, U5.6 (BAT-)
/+3V3: C3.2, R6.2, U1.3 (V_{DD}), U4.3V3
/+5V: C1.1, C2.1, J2.1, TP1.1 (1_1), U4.5V, U6.3 (+VOUT)
/BAT_MON: JP1.2 (B), U4.IO12
/PIR. SIG.: J2.2, JP3.1 (A), R1.1
/TEMP. SIG.: JP3.3 (B), R6.1, U1.2 (DQ)
GND: C1.2, C2.2, C3.1, C5.1, C6.2, J2.3, NT2.2, R1.2, R2.1, TP2.1 (1_1), U1.1 (GND), U4.GND2, U6.2 (GND)
unnamed: D2.2 (A), J1.1, JP2.2 (B), Q1.1 (G), R10.1, U5.1 (IN+)
unnamed: C5.2, C6.1, D2.1 (K), Q1.3 (S), R10.2, TP3.1 (1_1), U6.1 (+VIN)
unnamed: J1.2, U5.2 (IN-)
unnamed: JP1.1 (A), R3.2, R4.1
unnamed: JP2.1 (A), R2.2
unnamed: JP3.2 (C), U4.IO13
unnamed: Q1.2 (D), U5.3 (OUT+)
unnamed: BT1.P, Q5.3 (S), R14.1

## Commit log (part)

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2026-04-30 initial commit – 2026-04-30
2026-05-12 Add configurable battery monitor and improve OTA robustness
2026-05-12 Clean repo metadata and ignore local editor files
2026-05-16 Add battery two-point calibration with Telegram commands and fix reboot behavior
    - Implement persistent per-camera battery calibration via NVS with two-point linear model
    - Add Telegram commands: /battcal, /battcalset, /battcalclear (with /batcal* aliases)
    - Update measured divider resistor values (1.95M / 1.024M)
    - Change /reboot to plain restart (remove OTA recovery arming)
    - Remove /ota_cancel command
    - Display raw and calibrated battery voltage in status messages
2026-05-16 Add KiCad hardware project (schematic and PCB layout)
    - Integrate BirdNest PCB design into repository
    - Include KiCad schematic (BirdNest_pcb.kicad_sch)
    - Include PCB layout (BirdNest_pcb.kicad_pcb)
    - Include project file (BirdNest_pcb.kicad_pro)
    - Update .gitignore to exclude KiCad temp files, backups, and lock files
2026-05-16 Update BirdNest firmware and PCB design
2026-05-16 Fix GPIO pin assignments in README: battery ADC GPIO12, correct camera pin mapping
2026-05-16 Add MQTT Telegram runtime config and topic control\n\n- Added /mqttset and /mqtttopic HTTP endpoints\n- Updated README with MQTT config section\n- Added mqtt_client.h/.cpp with Telegram support
2026-05-17 docs: align README and unify debug message verbosity
2026-05-29 Update docs with battery and hardware details
2026-05-29 Move hardware section to top of README
2026-05-29 Add short English project description to README
2026-05-29 Clarify wakeup-photo comments and fully clear MQTT topic config
2026-05-29 Commit all remaining changes
2026-06-06 Include camera label in Telegram debug messages
2026-06-06 Adjust sun times header configuration
2026-06-06 Update camera runtime behavior
2026-06-06 Refine PlatformIO environment settings
2026-06-06 Update main application flow
2026-06-06 Update README documentation
2026-06-19 Add detailed Copilot instructions grounded in actual implementation
